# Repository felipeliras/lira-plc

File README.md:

# lira-plc

## Disclaimer
This project includes CAD models provided by Phoenix Contact for integration into the PCB assembly. The CAD files are used in accordance with Phoenix Contact’s usage rights for the purpose of distributing and documenting this project. Phoenix Contact remains the owner and author of the original CAD files. All product names, logos, and trademarks are the property of their respective owners.

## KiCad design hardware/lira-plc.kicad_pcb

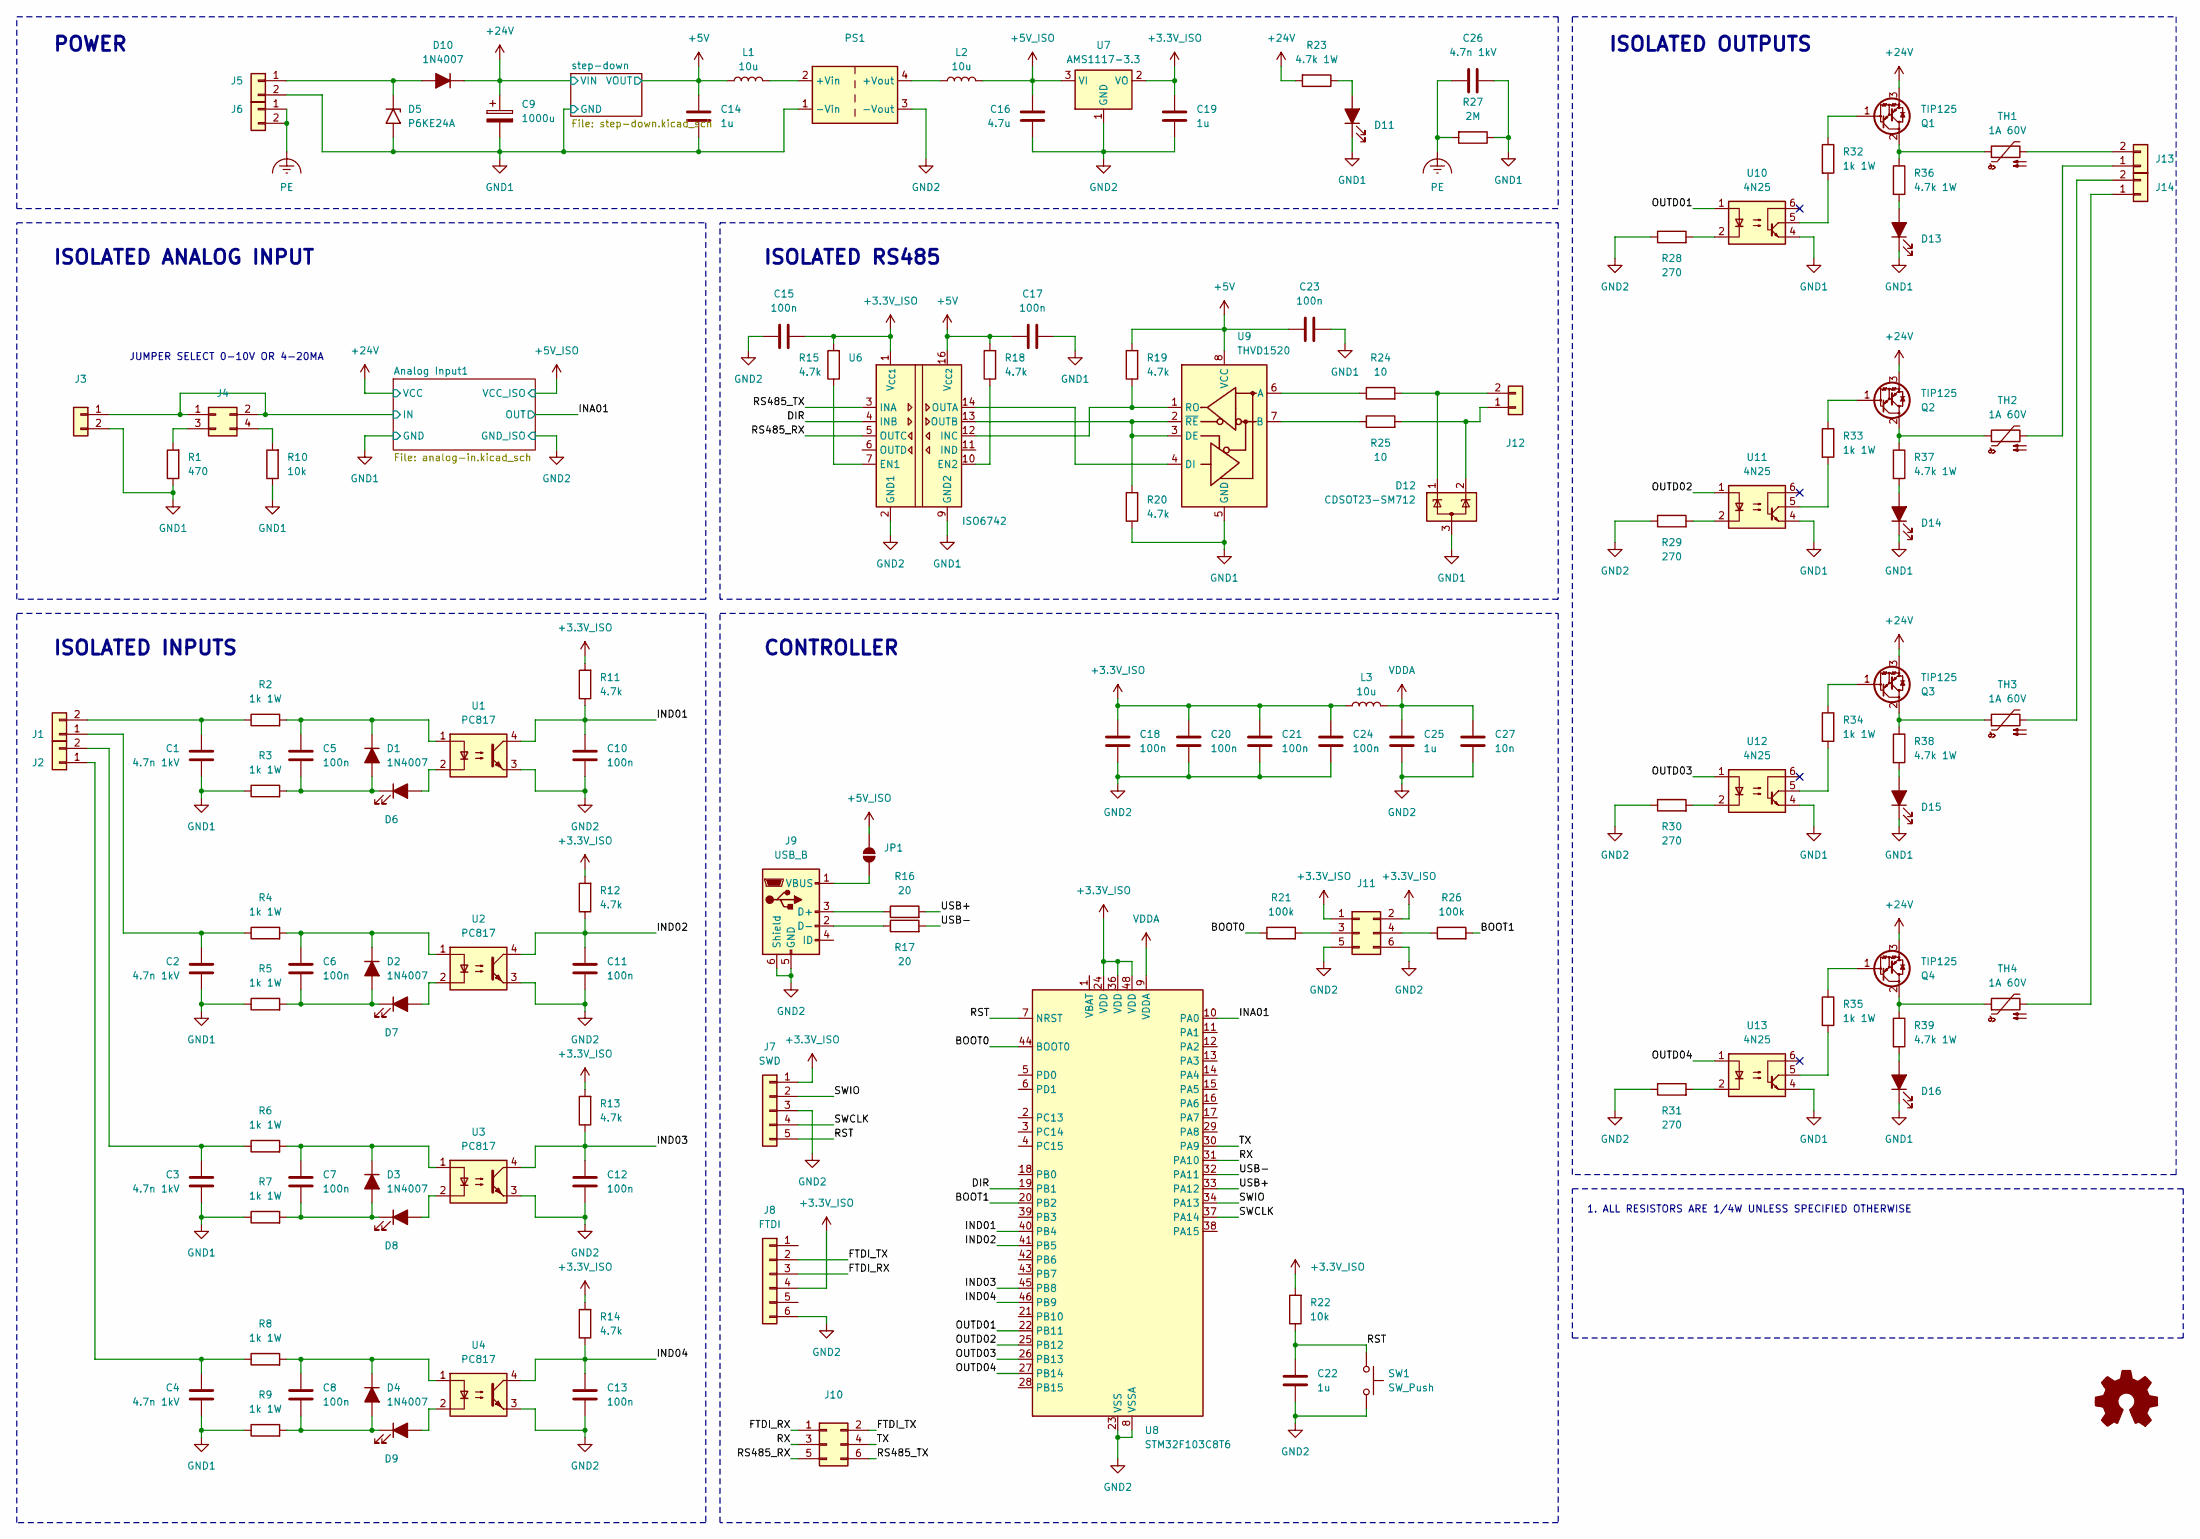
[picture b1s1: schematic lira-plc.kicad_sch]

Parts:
C1, C2, C3, C4, C26: 4.7n 1kV; C_Disc_D4.3mm_W1.9mm_P5.00mm
C5, C6, C7, C8, C10, C11, C12, C13, C15, C17, C18, C20, C21, C23, C24: 100n; C_0603_1608Metric_Pad1.08x0.95mm_HandSolder
C9: 1000u; CP_Radial_D10.0mm_P5.00mm
C14, C19, C22, C25: 1u; C_0603_1608Metric_Pad1.08x0.95mm_HandSolder
C16: 4.7u; C_1206_3216Metric_Pad1.33x1.80mm_HandSolder
C27: 10n; C_0603_1608Metric_Pad1.08x0.95mm_HandSolder
D1, D2, D3, D4: 1N4007; D_DO-41_SOD81_P2.54mm_Vertical_AnodeUp
D5: P6KE24A; D_DO-41_SOD81_P2.54mm_Vertical_AnodeUp
D6, D7, D8, D9, D11, D13, D14, D15, D16: LED_Filled; LED_D3.0mm
D10: 1N4007; D_DO-41_SOD81_P5.08mm_Vertical_AnodeUp
D12: CDSOT23-SM712; SOT-23-3
J1, J2, J3, J5, J6, J12, J13, J14: Conn_01x02; Metaltex-BR0
J4: Conn_02x02_Counter_Clockwise; PinHeader_2x02_P2.54mm_Vertical
J7: SWD; PinHeader_1x05_P2.54mm_Vertical
J8: FTDI; PinHeader_1x07_P2.54mm_Vertical
J9: USB_B; USB_Micro-B_Amphenol_10118193-0001LF_Horizontal
J10, J11: Conn_02x03_Odd_Even; PinHeader_2x03_P2.54mm_Vertical
JP1: SolderJumper_2_Open; SolderJumper-2_P1.3mm_Open_RoundedPad1.0x1.5mm
L1, L2, L3: 10u; L_1206_3216Metric_Pad1.42x1.75mm_HandSolder
PS1: Converter_DCDC_Murata_MEE1SxxxxSC_THT
Q1, Q2, Q3, Q4: TIP125; TO-220-3_Vertical
R1: 470; R_0603_1608Metric_Pad0.98x0.95mm_HandSolder
R2, R3, R4, R5, R6, R7, R8, R9, R32, R33, R34, R35: 1k 1W; R_Axial_DIN0207_L6.3mm_D2.5mm_P2.54mm_Vertical
R10, R22: 10k; R_0603_1608Metric_Pad0.98x0.95mm_HandSolder
R11, R12, R13, R14, R15, R18, R19, R20: 4.7k; R_0603_1608Metric_Pad0.98x0.95mm_HandSolder
R16, R17: 20; R_0603_1608Metric_Pad0.98x0.95mm_HandSolder
R21, R26: 100k; R_0603_1608Metric_Pad0.98x0.95mm_HandSolder
R23, R36, R37, R38, R39: 4.7k 1W; R_Axial_DIN0207_L6.3mm_D2.5mm_P2.54mm_Vertical
R24, R25: 10; R_0603_1608Metric_Pad0.98x0.95mm_HandSolder
R27: 2M; R_Axial_DIN0207_L6.3mm_D2.5mm_P2.54mm_Vertical
R28, R29, R30, R31: 270; R_0603_1608Metric_Pad0.98x0.95mm_HandSolder
SW1: SW_Push; SW_Tactile_SPST_NO_Straight_CK_PTS636Sx25SMTRLFS
TH1, TH2, TH3, TH4: 1A 60V; Fuse_Bourns_MF-RHT500
U1, U2, U3, U4: PC817; DIP-4_W7.62mm
U6: ISO6742; SOIC-16W_7.5x10.3mm_P1.27mm
U7: AMS1117-3.3; SOT-223-3_TabPin2
U8: STM32F103C8T6; LQFP-48_7x7mm_P0.5mm
U9: THVD1520; SOIC-8_3.9x4.9mm_P1.27mm
U10, U11, U12, U13: 4N25; DIP-6_W7.62mm

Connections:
+3.3V_ISO: C15.1, C18.1, C19.1, C20.1, C21.1, C24.1, J7.1, J8.4, J11.1, J11.2, L3.1, R11.2, R12.2, R13.2, R14.2, R15.2, R22.2, U6.1 (V_{CC1}), U7.2 (VO), U8.24 (VDD), U8.36 (VDD), U8.48 (VDD)
+5V: C14.1, C17.2, C23.1, L1.1, R18.2, R19.2, U6.16 (V_{CC2}), U9.8 (VCC); also elsewhere on the board
+5V_ISO: C16.1, JP1.2 (B), L2.2, U7.3 (VI); also elsewhere on the board
+24V: C9.1, D10.1 (K), Q1.3 (E), Q2.3 (E), Q3.3 (E), Q4.3 (E), R23.2; also elsewhere on the board
/Analog Input1/IN: J3.1, J4.1, J4.2; also elsewhere on the board
/BOOT0: R21.1, U8.44 (BOOT0)
/BOOT1: R26.2, U8.20 (PB2)
/DIR: U6.4 (INB), U8.19 (PB1)
/FTDI_RX: J8.3, J10.1
/FTDI_TX: J8.2, J10.2
/INA01: U8.10 (PA0); also elsewhere on the board
/IND01: C10.1, R11.1, U1.4, U8.40 (PB4)
/IND02: C11.1, R12.1, U2.4, U8.41 (PB5)
/IND03: C12.1, R13.1, U3.4, U8.45 (PB8)
/IND04: C13.1, R14.1, U4.4, U8.46 (PB9)
/OUTD01: U8.22 (PB11), U10.1
/OUTD02: U8.25 (PB12), U11.1
/OUTD03: U8.26 (PB13), U12.1
/OUTD04: U8.27 (PB14), U13.1
/RS485_RX: J10.5, U6.5 (OUTC)
/RS485_TX: J10.6, U6.3 (INA)
/RST: C22.1, J7.5, R22.1, SW1.1, U8.7 (NRST)
/RX: J10.3, U8.31 (PA10)
/SWCLK: J7.4, U8.37 (PA14)
/SWIO: J7.2, U8.34 (PA13)
/TX: J10.4, U8.30 (PA9)
/USB+: R16.2, U8.33 (PA12)
/USB-: R17.2, U8.32 (PA11)
GND1: C1.2, C2.2, C3.2, C4.2, C9.2, C14.2, C17.1, C23.2, C26.2, D5.2 (A2), D11.1 (K), D12.3 (A), D13.1 (K), D14.1 (K), D15.1 (K), D16.1 (K), J3.2, J5.2, PS1.1 (-Vin), R1.1, R3.1, R5.1, R7.1, R9.1, R10.1, R20.1, R27.1, U6.9 (GND2), U6.15 (GND2), U9.5 (GND), U10.4, U11.4, U12.4, U13.4; also elsewhere on the board
GND2: C10.2, C11.2, C12.2, C13.2, C15.2, C16.2, C18.2, C19.2, C20.2, C21.2, C22.2, C24.2, C25.2, C27.2, J7.3, J8.6, J9.5 (GND), J9.6 (Shield), J11.5, J11.6, PS1.3 (-Vout), R28.1, R29.1, R30.1, R31.1, SW1.2, U1.3, U2.3, U3.3, U4.3, U6.2 (GND1), U6.8 (GND1), U7.1 (GND), U8.8 (VSSA), U8.23 (VSS), U8.35 (VSS), U8.47 (VSS); also elsewhere on the board
unnamed: C5.2, D1.2 (A), D6.1 (K), R3.2
unnamed: C5.1, D1.1 (K), R2.2, U1.1
unnamed: C6.2, D2.2 (A), D7.1 (K), R5.2
unnamed: C6.1, D2.1 (K), R4.2, U2.1
unnamed: C7.2, D3.2 (A), D8.1 (K), R7.2
unnamed: C7.1, D3.1 (K), R6.2, U3.1
unnamed: C8.2, D4.2 (A), D9.1 (K), R9.2
unnamed: C8.1, D4.1 (K), R8.2, U4.1
unnamed: D6.2 (A), U1.2
unnamed: D7.2 (A), U2.2
unnamed: D8.2 (A), U3.2
unnamed: D9.2 (A), U4.2
unnamed: D5.1 (A1), D10.2 (A), J5.1
unnamed: D11.2 (A), R23.1
unnamed: D13.2 (A), R36.2
unnamed: D14.2 (A), R37.2
unnamed: D15.2 (A), R38.2
unnamed: D16.2 (A), R39.2
unnamed: C2.1, J1.1, R4.1
unnamed: C1.1, J1.2, R2.1
unnamed: C4.1, J2.1, R8.1
unnamed: C3.1, J2.2, R6.1
unnamed: J4.3, R1.2
unnamed: J4.4, R10.2
unnamed: J9.3 (D+), R16.1
unnamed: J9.2 (D-), R17.1
unnamed: J9.1 (VBUS), JP1.1 (A)
unnamed: J11.3, R21.2
unnamed: J11.4, R26.1
unnamed: D12.2 (K), J12.1, R25.2
unnamed: D12.1 (K), J12.2, R24.2
unnamed: J13.1, TH2.2
unnamed: J13.2, TH1.2
unnamed: J14.1, TH4.2
unnamed: J14.2, TH3.2
unnamed: L1.2, PS1.2 (+Vin)
unnamed: L2.1, PS1.4 (+Vout)
unnamed: Q1.1 (B), R32.1
unnamed: Q1.2 (C), R36.1, TH1.1
unnamed: Q2.1 (B), R33.1
unnamed: Q2.2 (C), R37.1, TH2.1
unnamed: Q3.1 (B), R34.1
unnamed: Q3.2 (C), R38.1, TH3.1
unnamed: Q4.1 (B), R35.1
unnamed: Q4.2 (C), R39.1, TH4.1
unnamed: R28.2, U10.2
unnamed: R29.2, U11.2
unnamed: R30.2, U12.2
unnamed: R31.2, U13.2
unnamed: R32.2, U10.5
unnamed: R33.2, U11.5
unnamed: R34.2, U12.5
unnamed: R35.2, U13.5
unnamed: R15.1, U6.7 (EN1)
unnamed: R18.1, U6.10 (EN2)
unnamed: R19.1, U6.12 (INC), U9.1 (RO)
unnamed: U6.14 (OUTA), U9.4 (DI)
unnamed: R20.2, U6.13 (OUTB), U9.2 (~RE), U9.3 (DE)
unnamed: R24.1, U9.6 (A)
unnamed: R25.1, U9.7 (B)
PE: C26.1, J6.1, J6.2, R27.2
VDDA: C25.1, C27.1, L3.2, U8.9 (VDDA)

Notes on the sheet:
POWER
JUMPER SELECT 0-10V OR 4-20MA
ISOLATED ANALOG INPUT
ISOLATED OUTPUTS
ISOLATED INPUTS
CONTROLLER
1. ALL RESISTORS ARE 1/4W UNLESS SPECIFIED OTHERWISE
ISOLATED RS485

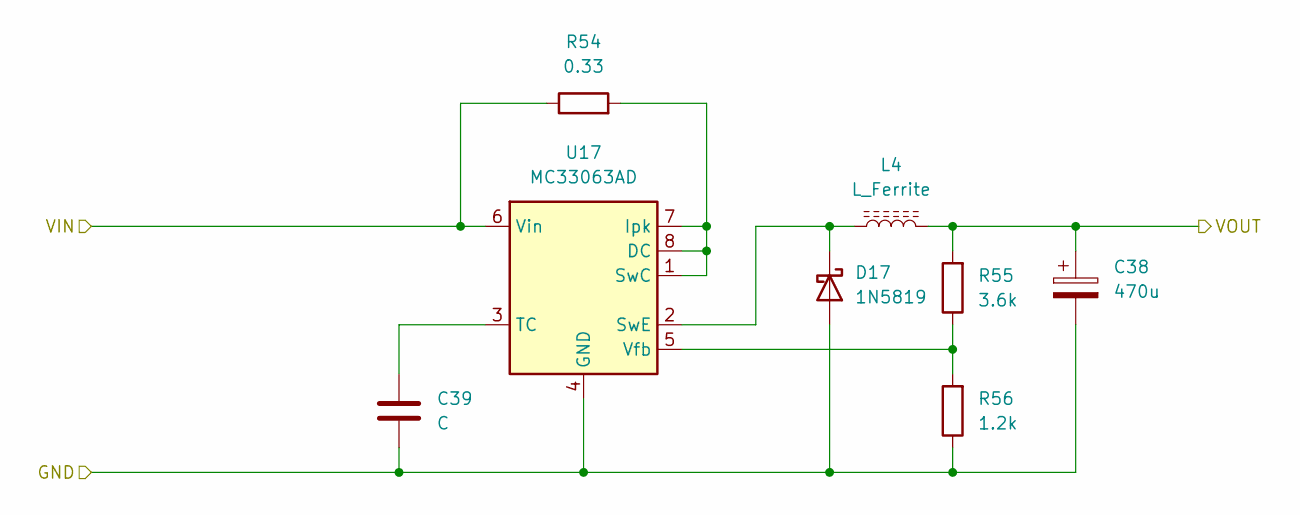
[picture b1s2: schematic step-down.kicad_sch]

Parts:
C38: 470u; CP_Radial_D8.0mm_P3.80mm
C39: C; C_0603_1608Metric_Pad1.08x0.95mm_HandSolder
D17: 1N5819; D_DO-41_SOD81_P2.54mm_Vertical_AnodeUp
L4: L_Ferrite; L_APV_ANR6045
R54: 0.33; R_Axial_DIN0207_L6.3mm_D2.5mm_P2.54mm_Vertical
R55: 3.6k; R_0603_1608Metric_Pad0.98x0.95mm_HandSolder
R56: 1.2k; R_0603_1608Metric_Pad0.98x0.95mm_HandSolder
U17: MC33063AD; SOIC-8_3.9x4.9mm_P1.27mm

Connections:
+5V: C38.1, L4.2, R55.2; also elsewhere on the board
+24V: R54.1, U17.6 (Vin); also elsewhere on the board
GND1: C38.2, C39.2, D17.2 (A), R56.1, U17.4 (GND); also elsewhere on the board
unnamed: D17.1 (K), L4.1, U17.2 (SwE)
unnamed: R54.2, U17.1 (SwC), U17.7 (Ipk), U17.8 (DC)
unnamed: C39.1, U17.3 (TC)
unnamed: R55.1, R56.2, U17.5 (Vfb)

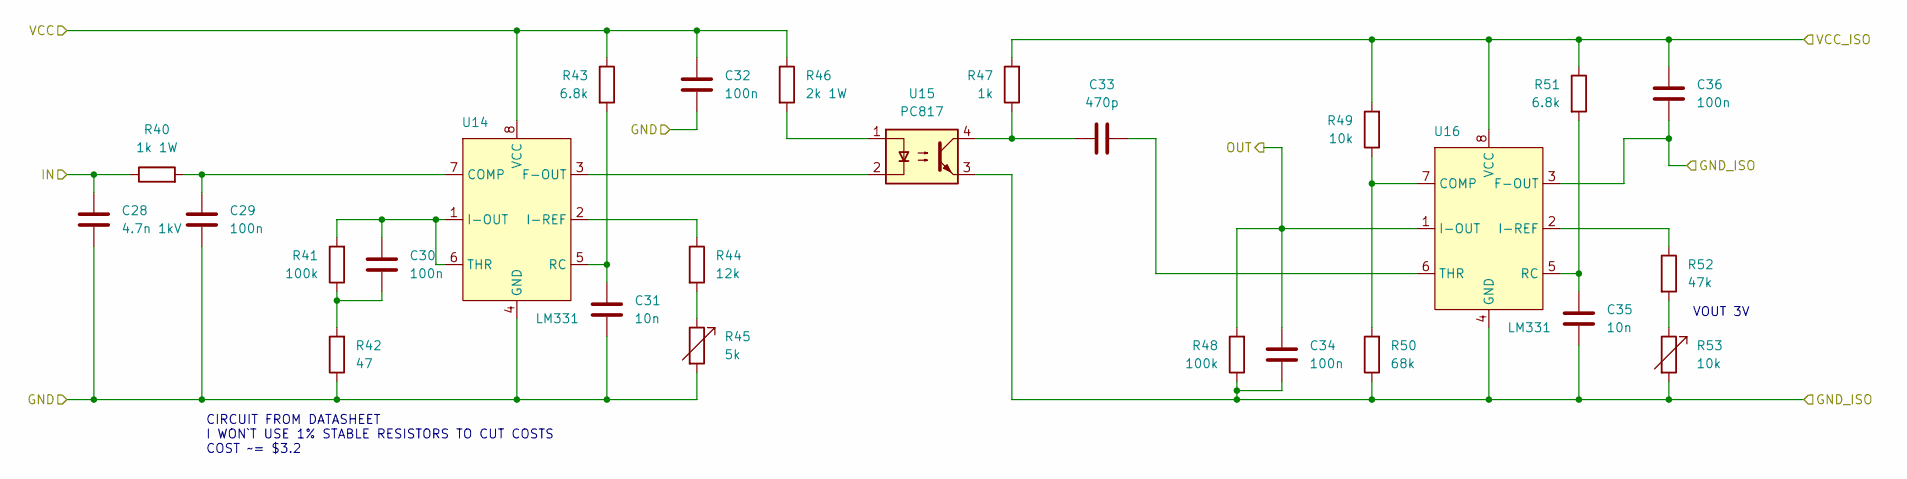
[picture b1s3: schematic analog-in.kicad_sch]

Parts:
C28: 4.7n 1kV; C_Disc_D4.3mm_W1.9mm_P5.00mm
C29, C30, C32, C34, C36: 100n; C_0603_1608Metric_Pad1.08x0.95mm_HandSolder
C31, C35: 10n; C_0603_1608Metric_Pad1.08x0.95mm_HandSolder
C33: 470p; C_0603_1608Metric_Pad1.08x0.95mm_HandSolder
R40: 1k 1W; R_Axial_DIN0207_L6.3mm_D2.5mm_P2.54mm_Vertical
R41, R48: 100k; R_0603_1608Metric_Pad0.98x0.95mm_HandSolder
R42: 47; R_0603_1608Metric_Pad0.98x0.95mm_HandSolder
R43, R51: 6.8k; R_0603_1608Metric_Pad0.98x0.95mm_HandSolder
R44: 12k; R_0603_1608Metric_Pad0.98x0.95mm_HandSolder
R45: 5k; Potentiometer_Bourns_TC33X_Vertical
R46: 2k 1W; R_Axial_DIN0207_L6.3mm_D2.5mm_P2.54mm_Vertical
R47: 1k; R_0603_1608Metric_Pad0.98x0.95mm_HandSolder
R49: 10k; R_0603_1608Metric_Pad0.98x0.95mm_HandSolder
R50: 68k; R_0603_1608Metric_Pad0.98x0.95mm_HandSolder
R52: 47k; R_0603_1608Metric_Pad0.98x0.95mm_HandSolder
R53: 10k; Potentiometer_Bourns_TC33X_Vertical
U14, U16: LM331; DIP-8_W7.62mm
U15: PC817; DIP-4_W7.62mm

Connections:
+5V_ISO: C36.2, R47.2, R49.2, R51.1, U16.8 (VCC); also elsewhere on the board
+24V: C32.2, R43.1, R46.1, U14.8 (VCC); also elsewhere on the board
/Analog Input1/IN: C28.1, R40.1; also elsewhere on the board
/INA01: C34.1, R48.2, U16.1 (I-OUT); also elsewhere on the board
GND1: C28.2, C29.2, C31.1, C32.1, R42.1, R45.2, U14.4 (GND); also elsewhere on the board
GND2: C34.2, C35.1, C36.1, R48.1, R50.1, R53.2, U15.3, U16.3 (F-OUT), U16.4 (GND); also elsewhere on the board
unnamed: C30.2, R41.1, R42.2
unnamed: C33.1, R47.1, U15.4
unnamed: R44.2, R45.1
unnamed: R46.2, U15.1
unnamed: R52.2, R53.1
unnamed: C29.1, R40.2, U14.7 (COMP)
unnamed: U14.3 (F-OUT), U15.2
unnamed: C30.1, R41.2, U14.1 (I-OUT), U14.6 (THR)
unnamed: R44.1, U14.2 (I-REF)
unnamed: C31.2, R43.2, U14.5 (RC)
unnamed: R49.1, R50.2, U16.7 (COMP)
unnamed: R52.1, U16.2 (I-REF)
unnamed: C35.2, R51.2, U16.5 (RC)
unnamed: C33.2, U16.6 (THR)

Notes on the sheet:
VOUT 3V
CIRCUIT FROM DATASHEET I WON`T USE 1% STABLE RESISTORS TO CUT COSTS COST ~= $3.2

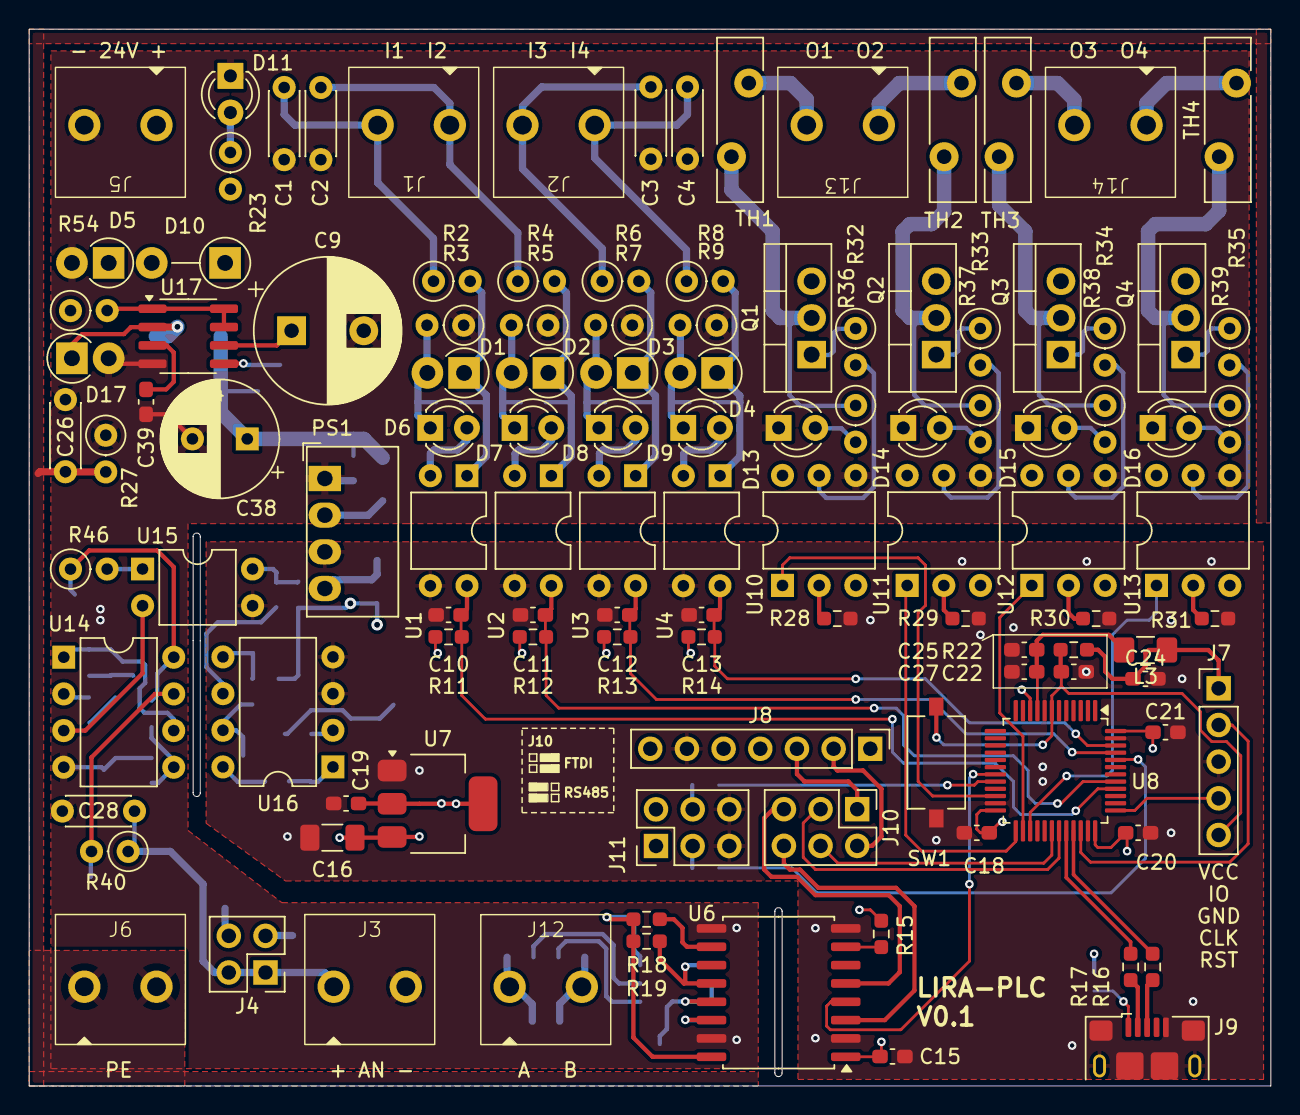
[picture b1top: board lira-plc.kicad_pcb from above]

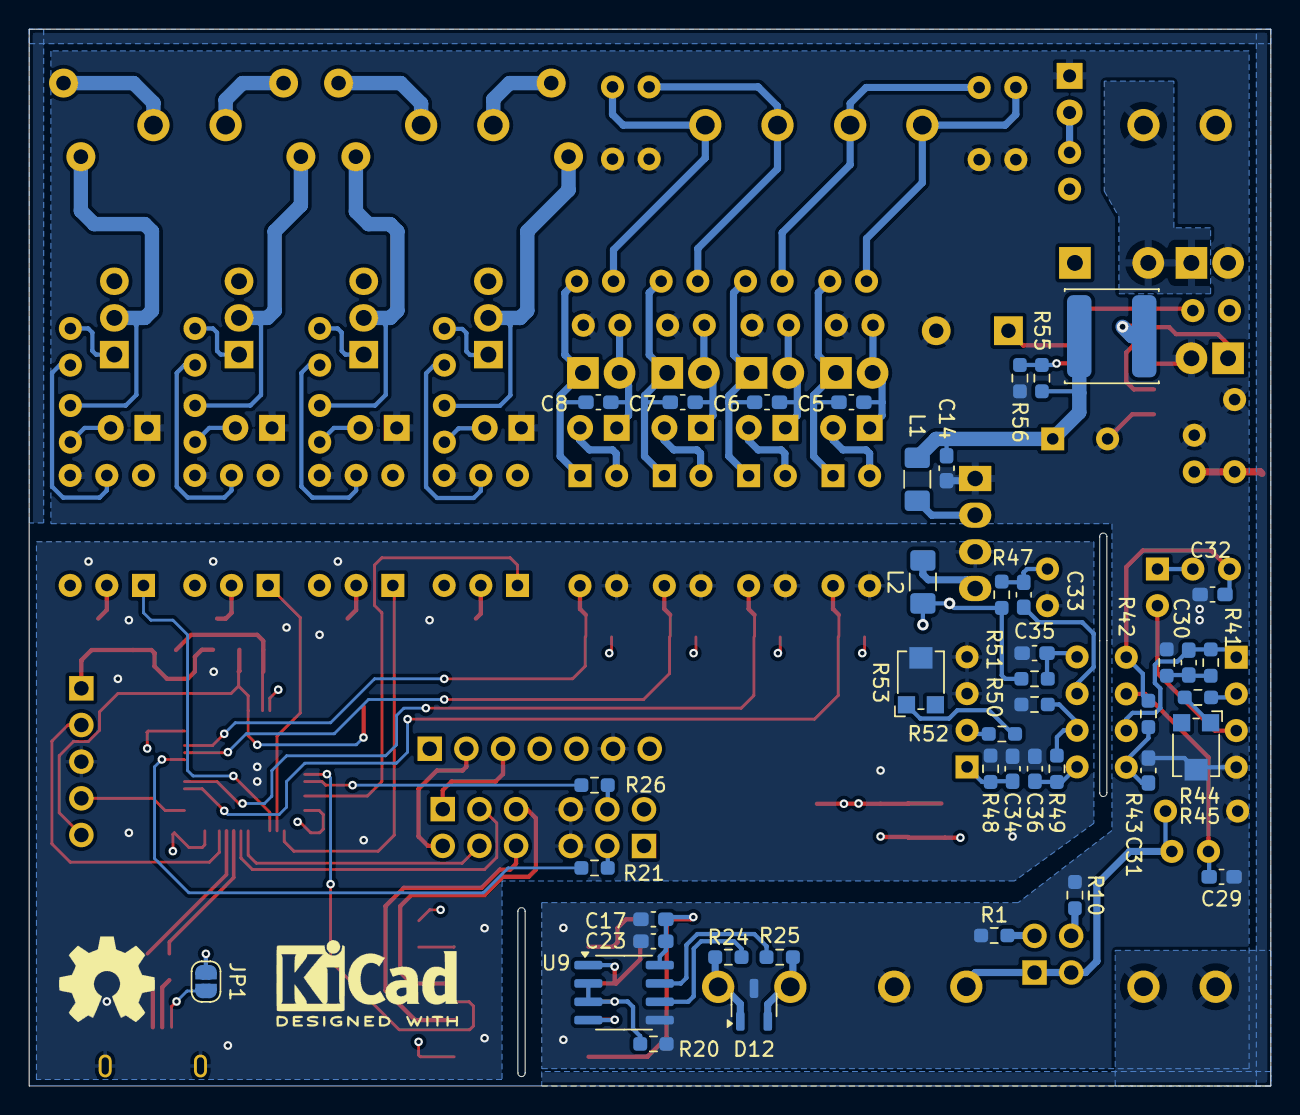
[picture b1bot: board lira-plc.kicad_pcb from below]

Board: 4 copper layers, 86.0 x 73.2 mm, 156 parts (42 on the bottom side), 110 nets.

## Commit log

2024-12-10 Input Draft
2024-12-12 component values
2024-12-13 power supply and output
2024-12-13 organizing the circuit
2024-12-14 analog input finished
2024-12-14 power supply simplified to just 24VDC
2024-12-14 Update LICENSE
2024-12-14 analog input and power supply
2024-12-15 support circuit for microcontroller
2024-12-15 saving the rs485 transceiver
2024-12-17 modbus rs485 added
2024-12-17 annotate schematic
2024-12-17 capacitor in power supply
2024-12-28 end of schematic drawing
    isolated modbus and controller circuit added
2025-01-03 footprint selection for all components
2025-01-04 input routed
2025-01-05 smaller size io
2025-01-05 power components placement
2025-01-05 75% routed and minor fixes
    Some wrong ground connections fixed, all external circuit routed, references organized
2025-01-07 pcb routed, some minor fixes, needs revision before gerbers
2025-01-07 Changed disclaimer
2025-01-09 gerber files
2025-10-17 changed: improved schematics following Andrew Greenberg's best practices at Kicon 2025
    Useful Schematics Or, “Don’t make me want to murder you” Andrew Greenberg Senior Instructor, Portland State University adg4@pdx.edu
    KiCon North America 2025 Day 2: https://www.youtube.com/watch?v=h8s6T9pnWlY&t=23595s
